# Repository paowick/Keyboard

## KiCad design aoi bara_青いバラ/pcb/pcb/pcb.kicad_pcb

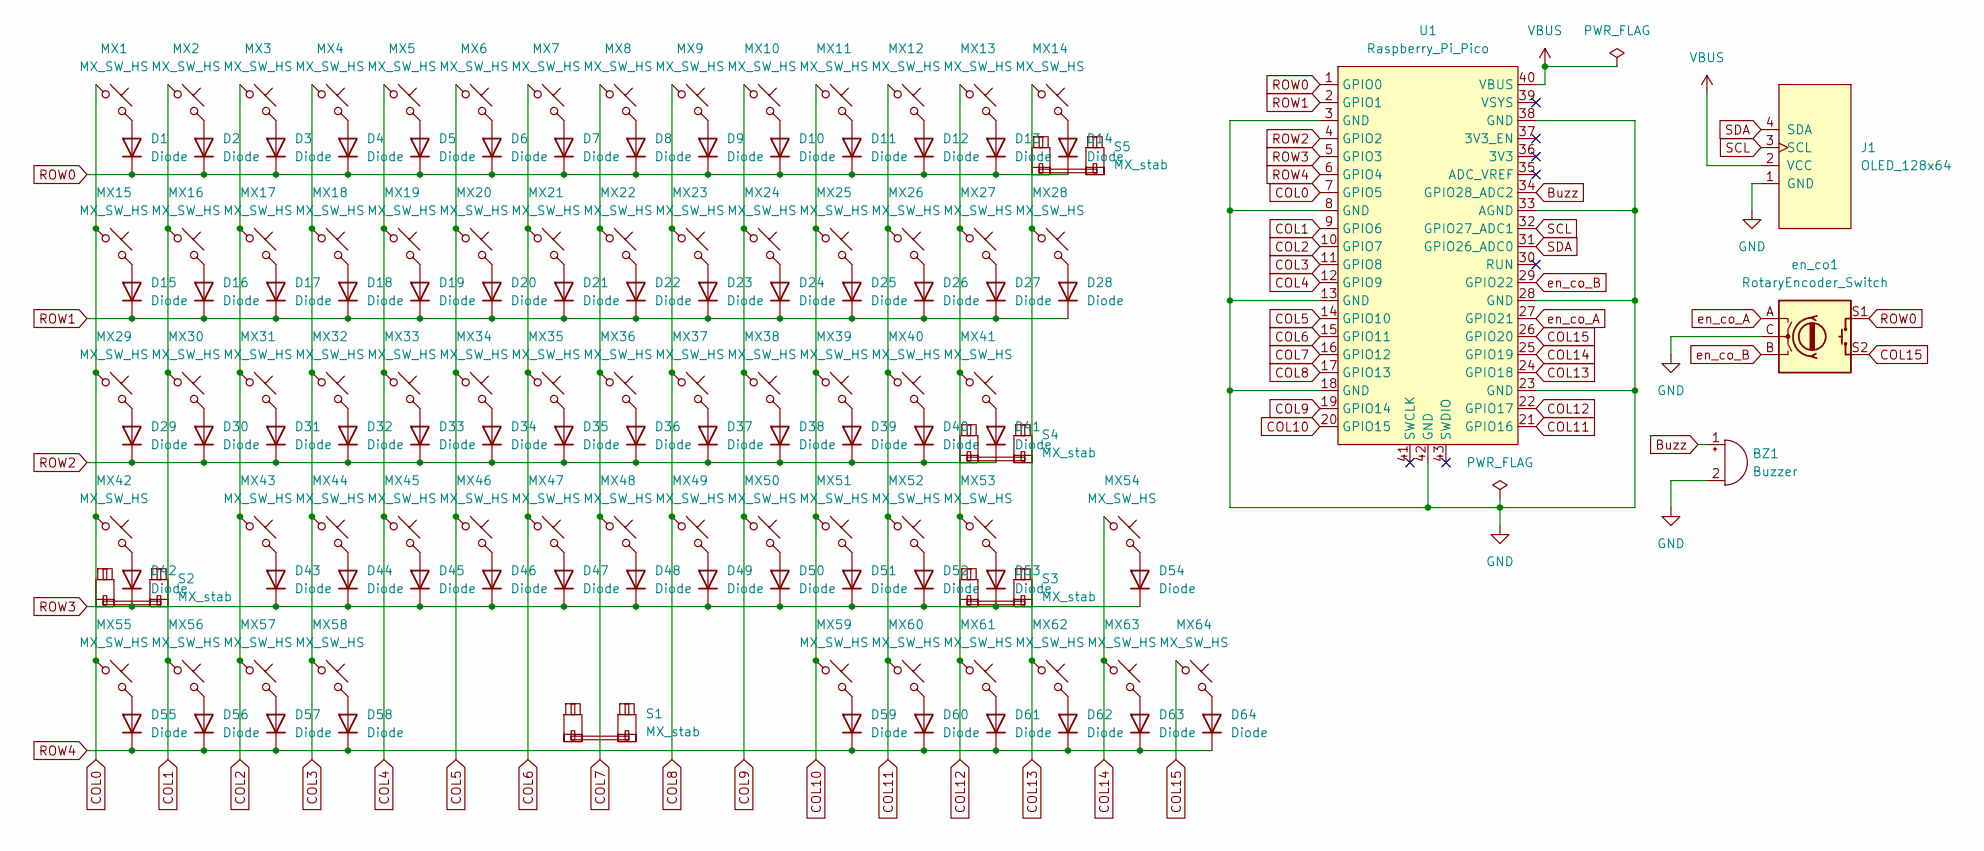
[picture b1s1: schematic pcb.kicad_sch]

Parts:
BZ1: Buzzer; Buzzer_12x9.5RM7.6
D1, D2, D3, D4, D5, D6, D7, D8, D9, D10, D11, D12, D13, D14, D15, D16, D17, D18, D19, D20, D21, D22, D23, D24, D25, D26, D27, D28, D29, D30, D31, D32, D33, D34, D35, D36, D37, D38, D39, D40, D41, D42, D43, D44, D45, D46, D47, D48, D49, D50, D51, D52, D53, D54, D55, D56, D57, D58, D59, D60, D61, D62, D63, D64: Diode; Diode_DO-35
J1: OLED_128x64
MX1, MX2, MX3, MX4, MX5, MX6, MX7, MX8, MX9, MX10, MX11, MX12, MX13, MX14, MX15, MX16, MX17, MX18, MX19, MX20, MX21, MX22, MX23, MX24, MX25, MX26, MX27, MX28, MX29, MX30, MX31, MX32, MX33, MX34, MX35, MX36, MX37, MX38, MX39, MX40, MX41, MX42, MX43, MX44, MX45, MX46, MX47, MX48, MX49, MX50, MX51, MX52, MX53, MX54, MX55, MX56, MX57, MX58, MX59, MX60, MX61, MX62, MX63, MX64: MX_SW_HS; SW_MX_HS_1u
S1: MX_stab; STAB_MX_P_6.25u
S2, S3, S4: MX_stab; STAB_MX_P_2.25u
S5: MX_stab; STAB_MX_P_2u
U1: Raspberry_Pi_Pico
en_co1: RotaryEncoder_Switch; ROT_Alps_EC11E-Switch

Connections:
Buzz: BZ1.1 (-), U1.34 (GPIO28_ADC2)
COL0: MX1.1, MX15.1, MX29.1, MX42.1, MX55.1, U1.7 (GPIO5)
COL1: MX2.1, MX16.1, MX30.1, MX56.1, U1.9 (GPIO6)
COL2: MX3.1, MX17.1, MX31.1, MX43.1, MX57.1, U1.10 (GPIO7)
COL3: MX4.1, MX18.1, MX32.1, MX44.1, MX58.1, U1.11 (GPIO8)
COL4: MX5.1, MX19.1, MX33.1, MX45.1, U1.12 (GPIO9)
COL5: MX6.1, MX20.1, MX34.1, MX46.1, U1.14 (GPIO10)
COL6: MX7.1, MX21.1, MX35.1, MX47.1, U1.15 (GPIO11)
COL7: MX8.1, MX22.1, MX36.1, MX48.1, U1.16 (GPIO12)
COL8: MX9.1, MX23.1, MX37.1, MX49.1, U1.17 (GPIO13)
COL9: MX10.1, MX24.1, MX38.1, MX50.1, U1.19 (GPIO14)
COL10: MX11.1, MX25.1, MX39.1, MX51.1, MX59.1, U1.20 (GPIO15)
COL11: MX12.1, MX26.1, MX40.1, MX52.1, MX60.1, U1.21 (GPIO16)
COL12: MX13.1, MX27.1, MX41.1, MX53.1, MX61.1, U1.22 (GPIO17)
COL13: MX14.1, MX28.1, MX62.1, U1.24 (GPIO18)
COL14: MX54.1, MX63.1, U1.25 (GPIO19)
COL15: MX64.1, U1.26 (GPIO20), en_co1.S2
GND: BZ1.2 (+), J1.1 (GND), U1.3 (GND), U1.8 (GND), U1.13 (GND), U1.18 (GND), U1.23 (GND), U1.28 (GND), U1.33 (AGND), U1.38 (GND), U1.42 (GND), en_co1.C
unnamed: D1.2 (A), MX1.2
unnamed: D2.2 (A), MX2.2
unnamed: D3.2 (A), MX3.2
unnamed: D4.2 (A), MX4.2
unnamed: D5.2 (A), MX5.2
unnamed: D6.2 (A), MX6.2
unnamed: D7.2 (A), MX7.2
unnamed: D8.2 (A), MX8.2
unnamed: D9.2 (A), MX9.2
unnamed: D10.2 (A), MX10.2
unnamed: D11.2 (A), MX11.2
unnamed: D12.2 (A), MX12.2
unnamed: D13.2 (A), MX13.2
unnamed: D14.2 (A), MX14.2
unnamed: D15.2 (A), MX15.2
unnamed: D16.2 (A), MX16.2
unnamed: D17.2 (A), MX17.2
unnamed: D18.2 (A), MX18.2
unnamed: D19.2 (A), MX19.2
unnamed: D20.2 (A), MX20.2
unnamed: D21.2 (A), MX21.2
unnamed: D22.2 (A), MX22.2
unnamed: D23.2 (A), MX23.2
unnamed: D24.2 (A), MX24.2
unnamed: D25.2 (A), MX25.2
unnamed: D26.2 (A), MX26.2
unnamed: D27.2 (A), MX27.2
unnamed: D28.2 (A), MX28.2
unnamed: D29.2 (A), MX29.2
unnamed: D30.2 (A), MX30.2
unnamed: D31.2 (A), MX31.2
unnamed: D32.2 (A), MX32.2
unnamed: D33.2 (A), MX33.2
unnamed: D34.2 (A), MX34.2
unnamed: D35.2 (A), MX35.2
unnamed: D36.2 (A), MX36.2
unnamed: D37.2 (A), MX37.2
unnamed: D38.2 (A), MX38.2
unnamed: D39.2 (A), MX39.2
unnamed: D40.2 (A), MX40.2
unnamed: D41.2 (A), MX41.2
unnamed: D42.2 (A), MX42.2
unnamed: D43.2 (A), MX43.2
unnamed: D44.2 (A), MX44.2
unnamed: D45.2 (A), MX45.2
unnamed: D46.2 (A), MX46.2
unnamed: D47.2 (A), MX47.2
unnamed: D48.2 (A), MX48.2
unnamed: D49.2 (A), MX49.2
unnamed: D50.2 (A), MX50.2
unnamed: D51.2 (A), MX51.2
unnamed: D52.2 (A), MX52.2
unnamed: D53.2 (A), MX53.2
unnamed: D54.2 (A), MX54.2
unnamed: D55.2 (A), MX55.2
unnamed: D56.2 (A), MX56.2
unnamed: D57.2 (A), MX57.2
unnamed: D58.2 (A), MX58.2
unnamed: D59.2 (A), MX59.2
unnamed: D60.2 (A), MX60.2
unnamed: D61.2 (A), MX61.2
unnamed: D62.2 (A), MX62.2
unnamed: D63.2 (A), MX63.2
unnamed: D64.2 (A), MX64.2
ROW0: D1.1 (K), D2.1 (K), D3.1 (K), D4.1 (K), D5.1 (K), D6.1 (K), D7.1 (K), D8.1 (K), D9.1 (K), D10.1 (K), D11.1 (K), D12.1 (K), D13.1 (K), D14.1 (K), U1.1 (GPIO0), en_co1.S1
ROW1: D15.1 (K), D16.1 (K), D17.1 (K), D18.1 (K), D19.1 (K), D20.1 (K), D21.1 (K), D22.1 (K), D23.1 (K), D24.1 (K), D25.1 (K), D26.1 (K), D27.1 (K), D28.1 (K), U1.2 (GPIO1)
ROW2: D29.1 (K), D30.1 (K), D31.1 (K), D32.1 (K), D33.1 (K), D34.1 (K), D35.1 (K), D36.1 (K), D37.1 (K), D38.1 (K), D39.1 (K), D40.1 (K), D41.1 (K), U1.4 (GPIO2)
ROW3: D42.1 (K), D43.1 (K), D44.1 (K), D45.1 (K), D46.1 (K), D47.1 (K), D48.1 (K), D49.1 (K), D50.1 (K), D51.1 (K), D52.1 (K), D53.1 (K), D54.1 (K), U1.5 (GPIO3)
ROW4: D55.1 (K), D56.1 (K), D57.1 (K), D58.1 (K), D59.1 (K), D60.1 (K), D61.1 (K), D62.1 (K), D63.1 (K), D64.1 (K), U1.6 (GPIO4)
SCL: J1.3 (SCL), U1.32 (GPIO27_ADC1)
SDA: J1.4 (SDA), U1.31 (GPIO26_ADC0)
VBUS: J1.2 (VCC), U1.40 (VBUS)
en_co_A: U1.27 (GPIO21), en_co1.A
en_co_B: U1.29 (GPIO22), en_co1.B

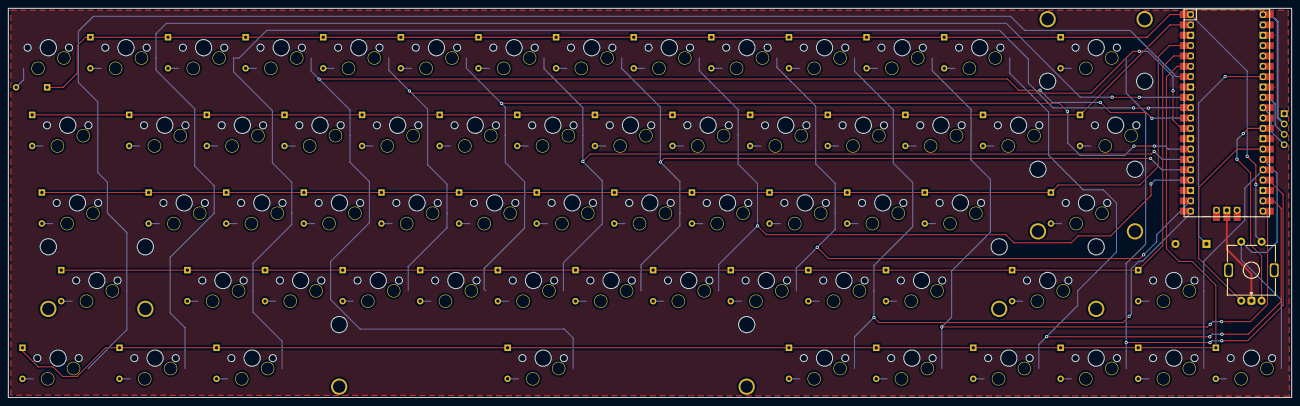
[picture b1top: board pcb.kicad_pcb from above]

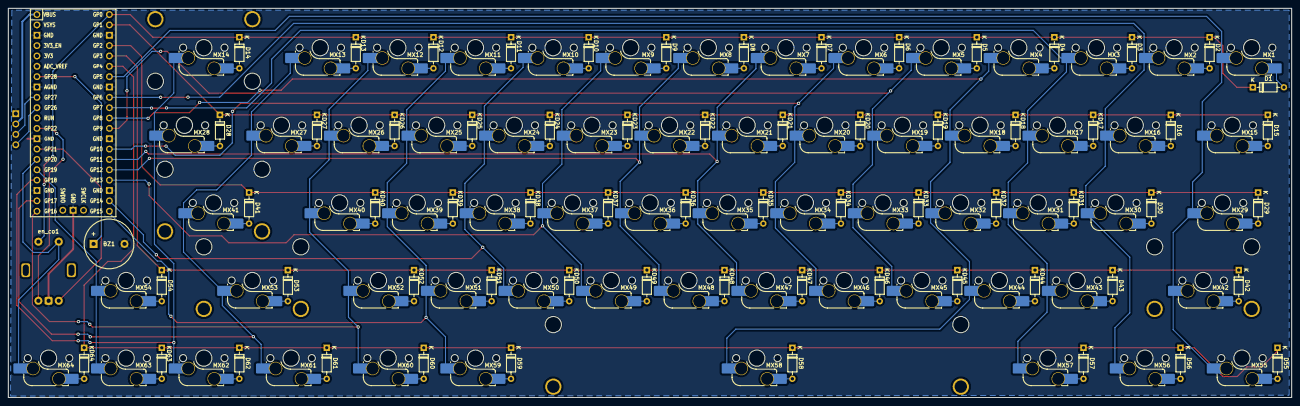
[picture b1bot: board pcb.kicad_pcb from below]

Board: 2 copper layers, 315.0 x 95.5 mm, 137 parts (129 on the bottom side), 92 nets.

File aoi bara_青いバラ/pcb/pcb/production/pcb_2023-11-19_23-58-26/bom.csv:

Designator,Footprint,Quantity,Value,LCSC Part #
"D1, D10, D11, D12, D13, D14, D15, D16, D17, D18, D19, D2, D20, D21, D22, D23, D24, D25, D26, D27, D28, D29, D3, D30, D31, D32, D33, D34, D35, D36, D37, D38, D39, D4, D40, D41, D42, D43, D44, D45, D46, D47, D48, D49, D5, D50, D51, D52, D53, D54, D55, D56, D57, D58, D59, D6, D60, D61, D62, D63, D64, D7, D8, D9",Diode_DO-35,64,Diode,
J1,OLED_128x64,1,OLED_128x64,
"LED1, LED10, LED11, LED12, LED13, LED14, LED15, LED16, LED17, LED18, LED19, LED2, LED20, LED21, LED22, LED23, LED24, LED25, LED26, LED27, LED28, LED29, LED3, LED30, LED31, LED32, LED33, LED34, LED35, LED36, LED37, LED38, LED39, LED4, LED40, LED41, LED42, LED43, LED44, LED45, LED46, LED47, LED48, LED49, LED5, LED50, LED51, LED52, LED53, LED54, LED55, LED56, LED57, LED58, LED59, LED6, LED60, LED61, LED62, LED63, LED64, LED7, LED8, LED9",LED_WS2812B_PLCC4_5.0x5.0mm_P3.2mm,64,LED_WS2812B,
"MX1, MX10, MX11, MX12, MX13, MX14, MX15, MX16, MX17, MX18, MX19, MX2, MX20, MX21, MX22, MX23, MX24, MX25, MX26, MX27, MX28, MX29, MX3, MX30, MX31, MX32, MX33, MX34, MX35, MX36, MX37, MX38, MX39, MX4, MX40, MX41, MX42, MX43, MX44, MX45, MX46, MX47, MX48, MX49, MX5, MX50, MX51, MX52, MX53, MX54, MX55, MX56, MX57, MX58, MX59, MX6, MX60, MX61, MX62, MX63, MX64, MX7, MX8, MX9",SW_MX_HS_1u,64,MX_SW_HS,
S1,STAB_MX_P_6.25u,1,MX_stab,
"S2, S3, S4",STAB_MX_P_2.25u,3,MX_stab,
S5,STAB_MX_P_2u,1,MX_stab,
U1,Raspberry_Pi_Pico,1,Raspberry_Pi_Pico,
en_co1,ROT_Alps_EC11E-Switch,1,RotaryEncoder_Switch,

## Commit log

2023-11-22 init
2023-12-03 deleted: "aoi bara_\351\235\222\343\201\204\343\203\220\343\203\251/frimware/aoi_bara/aoi_bara.c" modified: "aoi bara_\351\235\222\343\201\204\343\203\220\343\203\251/frimware/aoi_bara/config.h" modi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
2023-12-03 deleted: "aoi bara_\351\235\222\343\201\204\343\203\220\343\203\251/pcb/pcb/#auto_saved_files#" deleted: "aoi bara_\351\235\222\343\201\204\343\203\220\343\203\251/pcb/pcb/_autosave-pcb.kicad_pcb" de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
2024-01-28 new file: "aoi bara_\351\235\222\343\201\204\343\203\220\343\203\251/pcb/pcb/#auto_saved_files#" new file: "aoi bara_\351\235\222\343\201\204\343\203\220\343\203\251/pcb/pcb/_autosave-pcb.kicad_pcb" 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
2024-01-28 deleted: "aoi bara_\351\235\222\343\201\204\343\203\220\343\203\251/pcb/pcb/#auto_saved_files#" deleted: "aoi bara_\351\235\222\343\201\204\343\203\220\343\203\251/pcb/pcb/_autosave-pcb.kicad_pcb" de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
2024-02-08 modified: "aoi bara_\351\235\222\343\201\204\343\203\220\343\203\251/frimware/aoi_bara/config.h" modified: "aoi bara_\351\235\222\343\201\204\343\203\220\343\203\251/frimware/aoi_bara/rules.mk" new f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
2024-02-12 new file: .DS_Store new file: "aoi bara_\351\235\222\343\201\204\343\203\220\343\203\251/.DS_Store" new file: "aoi bara_\351\235\222\343\201\204\343\203\220\343\203\251/frimware/.DS_Store" new file: 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
2024-02-13 deleted: "aoi bara_\351\235\222\343\201\204\343\203\220\343\203\251/pcb/pcb/pcb-backups/pcb-2023-11-20_000758.zip" new file: "aoi bara_\351\235\222\343\201\204\343\203\220\343\203\251/pcb/pcb/pcb-bac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
2024-03-05 deleted: "aoi bara_\351\235\222\343\201\204\343\203\220\343\203\251/pcb/pcb/pcb-backups/pcb-2023-11-22_215522.zip" deleted: "aoi bara_\351\235\222\343\201\204\343\203\220\343\203\251/pcb/pcb/pcb-back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
2024-03-08 add via
2024-03-09 modified: "aoi bara_\351\235\222\343\201\204\343\203\220\343\203\251/frimware/aoi_bara/keymaps/default/keymap.c"
2024-03-09 modified: "aoi bara_\351\235\222\343\201\204\343\203\220\343\203\251/frimware/aoi_bara/keymaps/default/keymap.c" modified: "aoi bara_\351\235\222\343\201\204\343\203\220\343\203\251/frimware/aoi_bara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
2024-03-10 sound
2024-03-10 modified: "aoi bara_\351\235\222\343\201\204\343\203\220\343\203\251/frimware/aoi_bara/config.h" modified: "aoi bara_\351\235\222\343\201\204\343\203\220\343\203\251/frimware/aoi_bara/via.json" new f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
2024-03-11 new file: "aoi bara_\351\235\222\343\201\204\343\203\220\343\203\251/ani/ADO/ado-ado-cute.gif" new file: "aoi bara_\351\235\222\343\201\204\343\203\220\343\203\251/ani/ADO/ezgif-5-8c00ee82fa-gif-png.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
2024-03-12 add animetion
2024-03-22 via keymap
2024-03-22 vial imprement
